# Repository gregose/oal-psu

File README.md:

# oal-psu
TSP7A47-based power supply

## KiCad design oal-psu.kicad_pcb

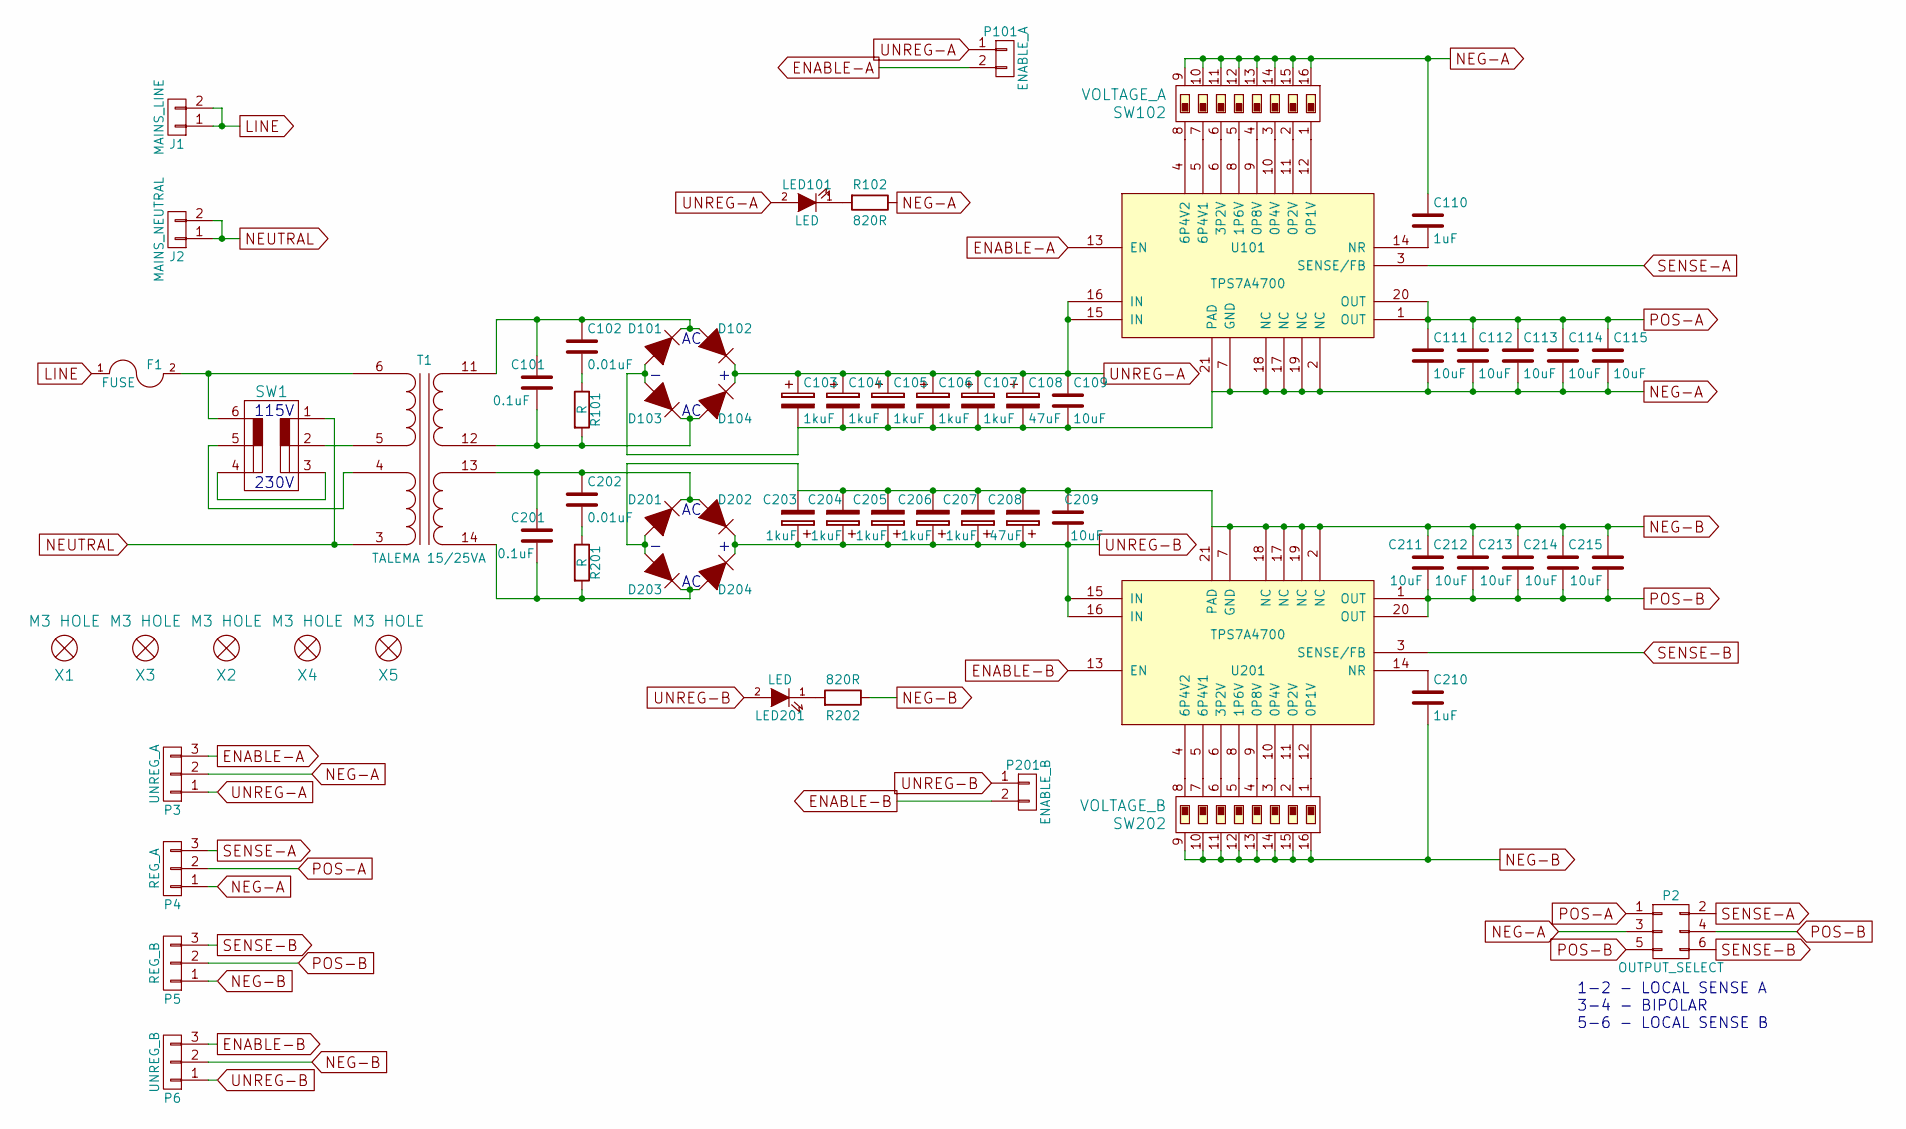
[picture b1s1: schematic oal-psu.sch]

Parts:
C101, C201: 0.1uF; TDK-B32529-63VAC
C102, C202: 0.01uF; TDK-B32529-63VAC
C103, C104, C106, C107, C203, C204, C205, C206: 1kuF; 35V-LYTIC-7.5-5
C105, C207: 1kuF; 35V-LYTIC-7.5-5-10snap
C108, C208: 47uF; TantalC_SizeD_EIA-7343_Reflow
C109, C111, C112, C113, C114, C115, C209, C211, C212, C213, C214, C215: 10uF; C_1206
C110, C210: 1uF; C_0805
D101, D102, D103, D104, D201, D202, D203, D204: DIODE-45; DO-221AC
F1: FUSE; LITTLEFUSE-0PTF0078P
J1: MAINS_LINE; PHEONIX_SPT_5-2POS
J2: MAINS_NEUTRAL; PHEONIX_SPT_5-2POS
LED101, LED201: LED; LED-1206
P2: OUTPUT_SELECT; Pin_Header_Straight_2x03
P3: UNREG_A; Phoenix-PTSM-0,5-3
P4: REG_A; Phoenix-PTSM-0,5-3
P5: REG_B; Phoenix-PTSM-0,5-3
P6: UNREG_B; Phoenix-PTSM-0,5-3
P101: ENABLE_A; Pin_Header_Straight_1x02
P201: ENABLE_B; Pin_Header_Straight_1x02
R101, R201: R; R_1210
R102, R202: 820R; R_0805
SW1: DPDT_SLIDE; CK_V80212MS02Q-VOLTAGE_SELECTOR
SW102: VOLTAGE_A; DIP8-HALF-PITCH-CHS-08B
SW202: VOLTAGE_B; DIP8-HALF-PITCH-CHS-08B
T1: TALEMA 15/25VA; TALEMA_70000K_35VA
U101, U201: TPS7A4700; PVQFN-N20
X1, X2, X3, X4, X5: M3 HOLE; MOUNTING_HOLE-M3

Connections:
ENABLE-A: P3.3, P101.2, U101.13 (EN)
ENABLE-B: P6.3, P201.2, U201.13 (EN)
LINE: F1.1, J1.1, J1.2
NEG-A: C103.2, C104.2, C105.2, C106.2, C107.2, C108.2, C109.2, C110.1, C111.2, C112.2, C113.2, C114.2, C115.2, D101.1 (ANODE), D103.1 (ANODE), P2.3, P3.2, P4.1, R102.1, SW102.9 (8B), SW102.10 (7B), SW102.11 (6B), SW102.12 (5B), SW102.13 (4B), SW102.14 (3B), SW102.15 (2B), SW102.16 (1B), U101.2 (NC), U101.7 (GND), U101.17 (NC), U101.18 (NC), U101.19 (NC), U101.21 (PAD)
NEG-B: C203.2, C204.2, C205.2, C206.2, C207.2, C208.2, C209.2, C210.1, C211.1, C212.1, C213.1, C214.1, C215.1, D201.1 (ANODE), D203.1 (ANODE), P5.1, P6.2, R202.1, SW202.9 (8B), SW202.10 (7B), SW202.11 (6B), SW202.12 (5B), SW202.13 (4B), SW202.14 (3B), SW202.15 (2B), SW202.16 (1B), U201.2 (NC), U201.7 (GND), U201.17 (NC), U201.18 (NC), U201.19 (NC), U201.21 (PAD)
NEUTRAL: J2.1, J2.2, SW1.1, T1.3 (PRIMARY2-NODOT)
unnamed: C101.1, C102.1, D101.2 (CATHODE), D102.1 (ANODE), T1.11 (SECONDARY1-DOT)
unnamed: C101.2, D103.2 (CATHODE), D104.1 (ANODE), R101.2, T1.12 (SECONDARY1-NODOT)
unnamed: C102.2, R101.1
unnamed: C110.2, U101.14 (NR)
unnamed: C201.1, C202.1, D201.2 (CATHODE), D202.1 (ANODE), T1.13 (SECONDARY2-DOT)
unnamed: C201.2, D203.2 (CATHODE), D204.1 (ANODE), R201.2, T1.14 (SECONDARY2-NODOT)
unnamed: C202.2, R201.1
unnamed: C210.2, U201.14 (NR)
unnamed: F1.2, SW1.6, T1.6 (PRIMARY1-DOT)
unnamed: LED101.1 (K), R102.2
unnamed: LED201.1 (K), R202.2
unnamed: SW1.2, T1.5 (PRIMARY1-NODOT)
unnamed: SW1.3, SW1.4
unnamed: SW1.5, T1.4 (PRIMARY2-DOT)
unnamed: SW102.1 (1A), U101.12 (0P1V)
unnamed: SW102.2 (2A), U101.11 (0P2V)
unnamed: SW102.3 (3A), U101.10 (0P4V)
unnamed: SW102.4 (4A), U101.9 (0P8V)
unnamed: SW102.5 (5A), U101.8 (1P6V)
unnamed: SW102.6 (6A), U101.6 (3P2V)
unnamed: SW102.7 (7A), U101.5 (6P4V1)
unnamed: SW102.8 (8A), U101.4 (6P4V2)
unnamed: SW202.1 (1A), U201.12 (0P1V)
unnamed: SW202.2 (2A), U201.11 (0P2V)
unnamed: SW202.3 (3A), U201.10 (0P4V)
unnamed: SW202.4 (4A), U201.9 (0P8V)
unnamed: SW202.5 (5A), U201.8 (1P6V)
unnamed: SW202.6 (6A), U201.6 (3P2V)
unnamed: SW202.7 (7A), U201.5 (6P4V1)
unnamed: SW202.8 (8A), U201.4 (6P4V2)
POS-A: C111.1, C112.1, C113.1, C114.1, C115.1, P2.1, P4.2, U101.1 (OUT), U101.20 (OUT)
POS-B: C211.2, C212.2, C213.2, C214.2, C215.2, P2.4, P2.5, P5.2, U201.1 (OUT), U201.20 (OUT)
SENSE-A: P2.2, P4.3, U101.3 (SENSE/FB)
SENSE-B: P2.6, P5.3, U201.3 (SENSE/FB)
UNREG-A: C103.1, C104.1, C105.1, C106.1, C107.1, C108.1, C109.1, D102.2 (CATHODE), D104.2 (CATHODE), LED101.2 (A), P3.1, P101.1, U101.15 (IN), U101.16 (IN)
UNREG-B: C203.1, C204.1, C205.1, C206.1, C207.1, C208.1, C209.1, D202.2 (CATHODE), D204.2 (CATHODE), LED201.2 (A), P6.1, P201.1, U201.15 (IN), U201.16 (IN)

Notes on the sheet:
1-2 - LOCAL SENSE A 3-4 - BIPOLAR 5-6 - LOCAL SENSE B
115V
230V

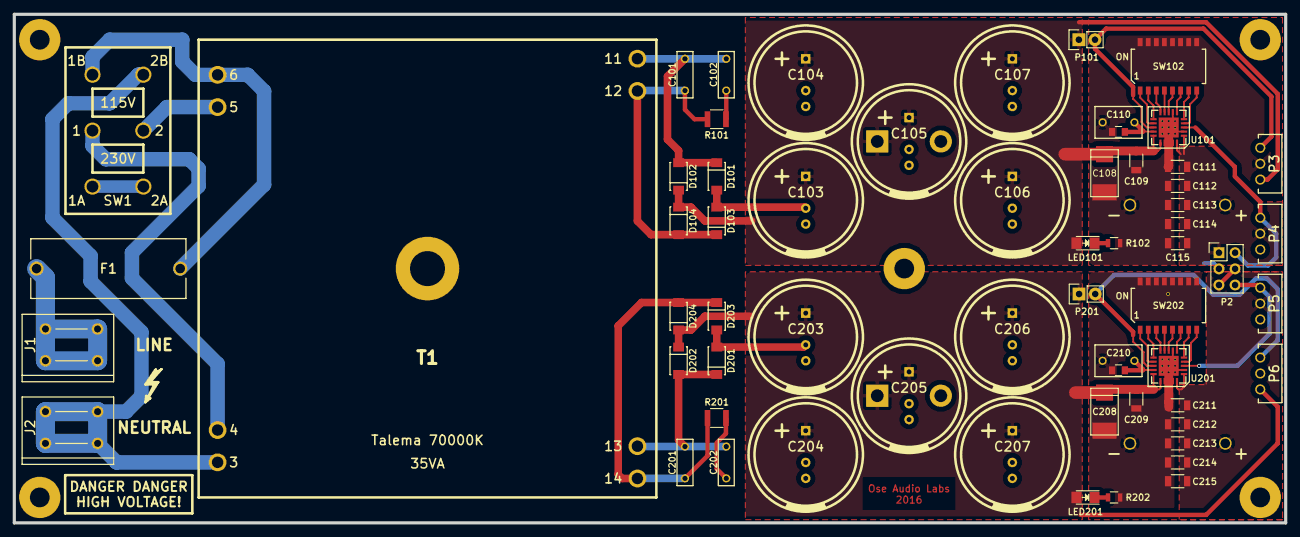
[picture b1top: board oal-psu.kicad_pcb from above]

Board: 2 copper layers, 200.0 x 80.0 mm, 65 parts (0 on the bottom side), 42 nets.

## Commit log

2016-02-17 intial schematic
2016-02-22 cap bank
2016-02-26 finalizing schematic
2016-02-27 mains voltage select switch
2016-02-29 finializing initial circuit pass
2016-03-03 initial layout work
2016-03-03 board outline
2016-03-03 more cleanup
2016-03-04 finished initial layout
2016-03-04 layout tweaks
2016-03-05 layout complete
2016-03-06 layout attempt 2
2016-03-06 beginning new layout for rail b
2016-03-09 new output connectors
2016-03-12 layout updates
